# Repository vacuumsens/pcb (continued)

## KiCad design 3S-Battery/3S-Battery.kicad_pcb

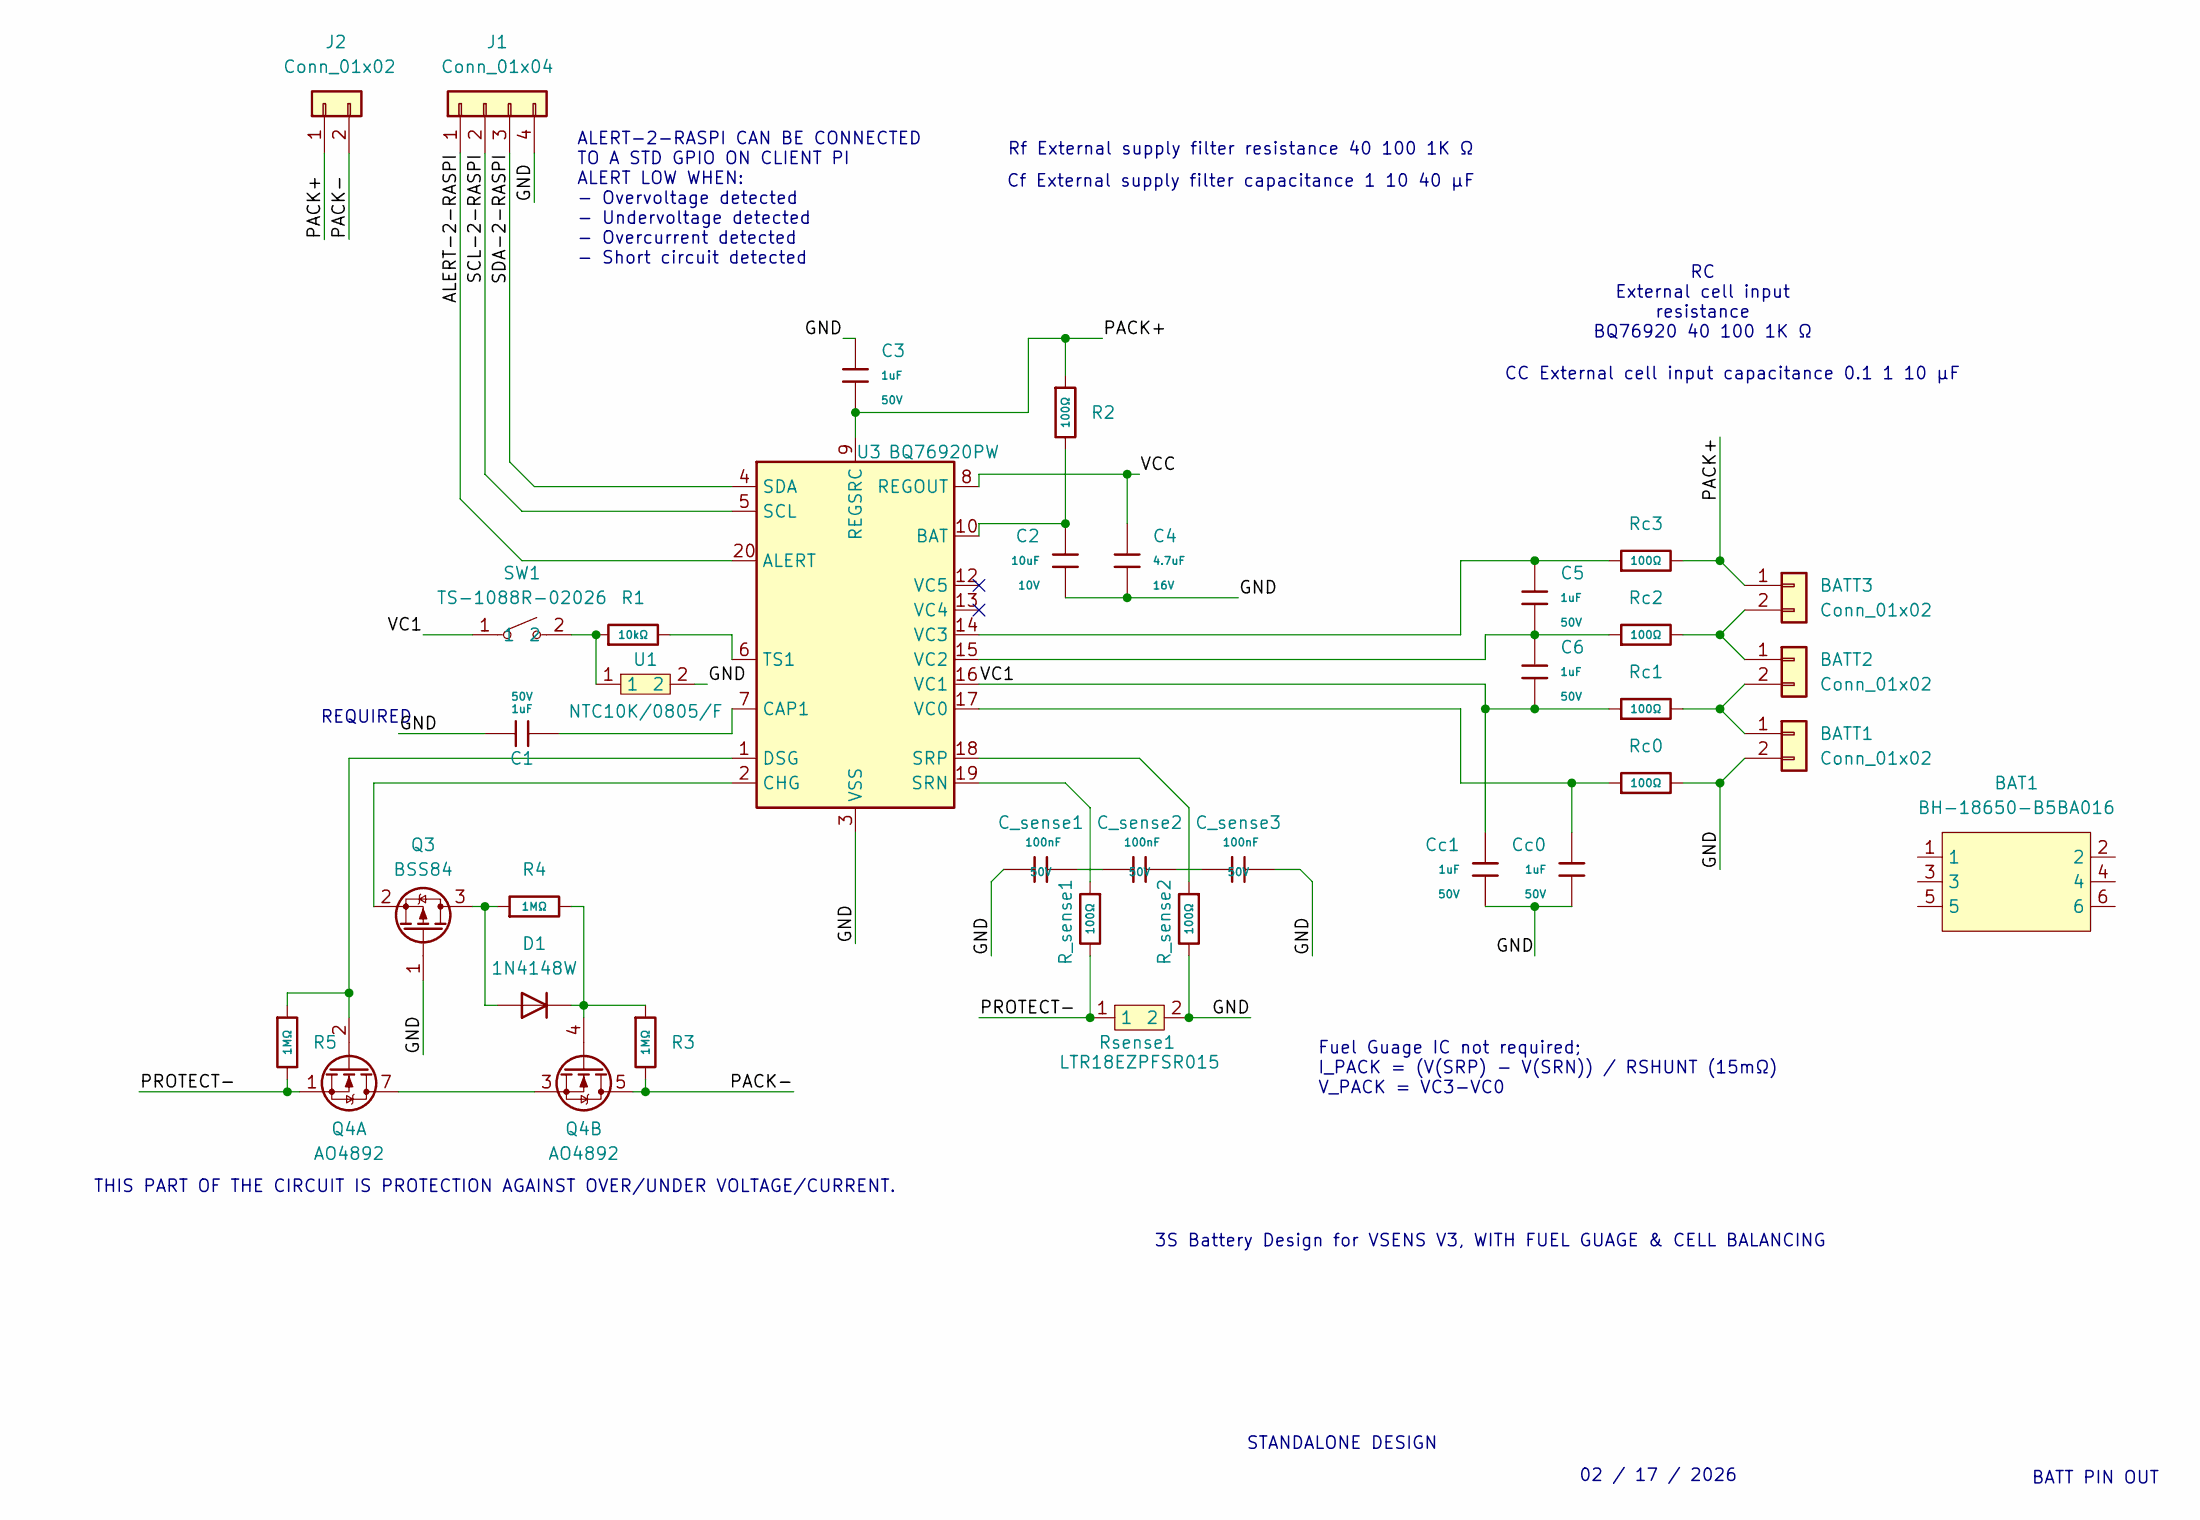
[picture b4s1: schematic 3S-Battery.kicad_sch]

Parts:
BAT1: BH-18650-B5BA016; BAT-SMD_BH-18650-B5BA016; LCSC Part C19184086
BATT1, BATT2, BATT3: Conn_01x02; PinHeader_1x02_P2.54mm_Vertical
C1: 1uF; C_1206; Voltage Rated 50V; Tolerance ±10%; Part CL31B105KBHNNNE; LCSC C1848
C2: 10uF; C_0603; Voltage Rated 10V; Tolerance ±10%; Part CL10A106KP8NNNC; LCSC C19702
C3, C5, C6: 1uF; C_0603; Voltage Rated 50V; Tolerance ±10%; Part CL10A105KB8NNNC; LCSC C15849
C4: 4.7uF; C_0603; Voltage Rated 16V; Tolerance ±10%; Part CL10A475KO8NNNC; LCSC C19666
C_sense1, C_sense2, C_sense3: 100nF; C_0603; Voltage Rated 50V; Tolerance ±10%; Part CC0603KRX7R9BB104; LCSC C14663
Cc0, Cc1: 1uF; C_0603; Voltage Rated 50V; Tolerance ±10%; Part CL10A105KB8NNNC; LCSC C15849
D1: 1N4148W; D_SOD-123
J1: Conn_01x04; PinHeader_1x04_P2.54mm_Vertical; LCSC Part C5116483
J2: Conn_01x02; PinHeader_1x02_P2.54mm_Vertical; LCSC Part C5360898
Q3: BSS84; SOT-23; LCSC Part C82079
Q4: AO4892; SOIC-8_3.9x4.9mm_P1.27mm; LCSC Part C357830
R1: 10kΩ; R_0603; Overload Voltage (Max) 75V; Tolerance ±1%; Part 0603WAF1002T5E; LCSC C25804
R2: 100Ω; R_0603; Overload Voltage (Max) 75V; Tolerance ±1%; Part 0603WAF1000T5E; LCSC C22775
R3, R4, R5: 1MΩ; R_0603; Overload Voltage (Max) 75V; Tolerance ±1%; Part 0603WAF1004T5E; LCSC C22935
R_sense1, R_sense2: 100Ω; R_0603; Overload Voltage (Max) 75V; Tolerance ±1%; Part 0603WAF1000T5E; LCSC C22775
Rc0, Rc1, Rc2, Rc3: 100Ω; R_0603; Overload Voltage (Max) 75V; Tolerance ±1%; Part 0603WAF1000T5E; LCSC C22775
Rsense1: LTR18EZPFSR015; R0612; LCSC Part C510175
SW1: TS-1088R-02026; SW-SMD_L3.9-W3.0-P4.45; LCSC Part C455280
U1: NTC10K/0805/F; R0805; LCSC Part C9900005726
U3: BQ76920PW; TSSOP-20_4.4x6.5mm_P0.65mm

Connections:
/ALERT-2-RASPI: J1.1, U3.20 (ALERT)
/GND: BATT1.2, C1.1, C2.1, C3.1, C4.2, C_sense1.1, C_sense3.2, Cc0.2, Cc1.2, J1.4, Q3.1 (G), R_sense2.2, Rc0.2, Rsense1.2, U1.2, U3.3 (VSS)
/PACK+: BATT3.1, C3.2, J2.1, R2.1, Rc3.2, U3.9 (REGSRC)
/PACK-: J2.2, Q4.5 (D2), Q4.6 (D2), R3.2
/PROTECT-: Q4.1 (S1), R5.2, R_sense1.2, Rsense1.1
/SCL-2-RASPI: J1.2, U3.5 (SCL)
/SDA-2-RASPI: J1.3, U3.4 (SDA)
/VC1: C6.2, Cc1.1, Rc1.1, SW1.1, U3.16 (VC1)
/VCC: C4.1, U3.8 (REGOUT)
unnamed: BATT1.1, BATT2.2, Rc1.2
unnamed: BATT2.1, BATT3.2, Rc2.2
unnamed: C_sense1.2, C_sense2.1
unnamed: C_sense2.2, C_sense3.1
unnamed: D1.2 (A), Q3.3 (D), R4.1
unnamed: D1.1 (K), Q4.4 (G2), R3.1, R4.2
unnamed: Q3.2 (S), U3.2 (CHG)
unnamed: Q4.2 (G1), R5.1, U3.1 (DSG)
unnamed: Q4.3 (S2), Q4.7 (D1), Q4.8 (D1)
unnamed: R1.1, SW1.2, U1.1
unnamed: C2.2, R2.2, U3.10 (BAT)
unnamed: C1.2, U3.7 (CAP1)
unnamed: R_sense1.1, U3.19 (SRN)
unnamed: R_sense2.1, U3.18 (SRP)
unnamed: R1.2, U3.6 (TS1)
unnamed: Cc0.1, Rc0.1, U3.17 (VC0)
unnamed: C5.2, C6.1, Rc2.1, U3.15 (VC2)
unnamed: C5.1, Rc3.1, U3.14 (VC3)

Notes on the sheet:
REQUIRED
02 / 17 / 2026
Fuel Guage IC not required; I_PACK = (V(SRP) - V(SRN)) / RSHUNT (15mΩ) V_PACK = VC3-VC0
STANDALONE DESIGN
RC External cell input resistance BQ76920 40 100 1K Ω
Rf External supply filter resistance 40 100 1K Ω
BATT PIN OUT
Cf External supply filter capacitance 1 10 40 µF
THIS PART OF THE CIRCUIT IS PROTECTION AGAINST OVER/UNDER VOLTAGE/CURRENT.
CC External cell input capacitance 0.1 1 10 µF
ALERT-2-RASPI CAN BE CONNECTED TO A STD GPIO ON CLIENT PI ALERT LOW WHEN: - Overvoltage detected - Undervoltage detected - Overcurrent detected - Short circuit detected
3S Battery Design for VSENS V3, WITH FUEL GUAGE & CELL BALANCING

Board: 2 copper layers, 35 parts (0 on the bottom side), 27 nets, no tracks yet.

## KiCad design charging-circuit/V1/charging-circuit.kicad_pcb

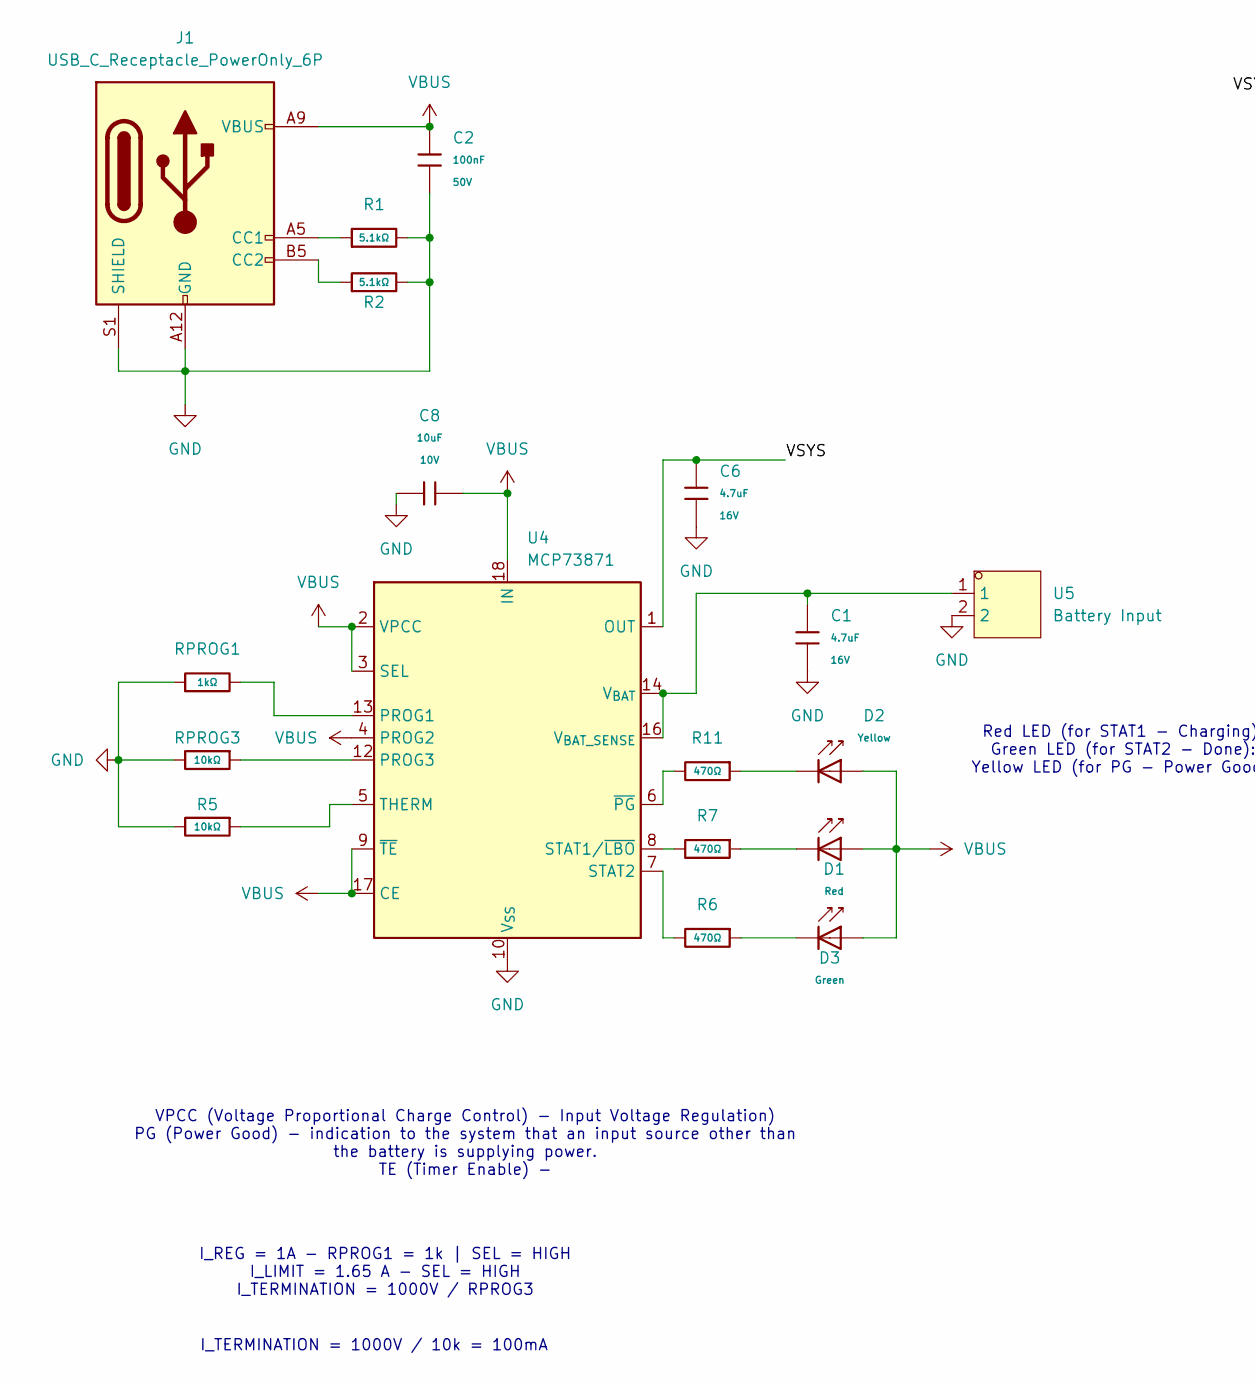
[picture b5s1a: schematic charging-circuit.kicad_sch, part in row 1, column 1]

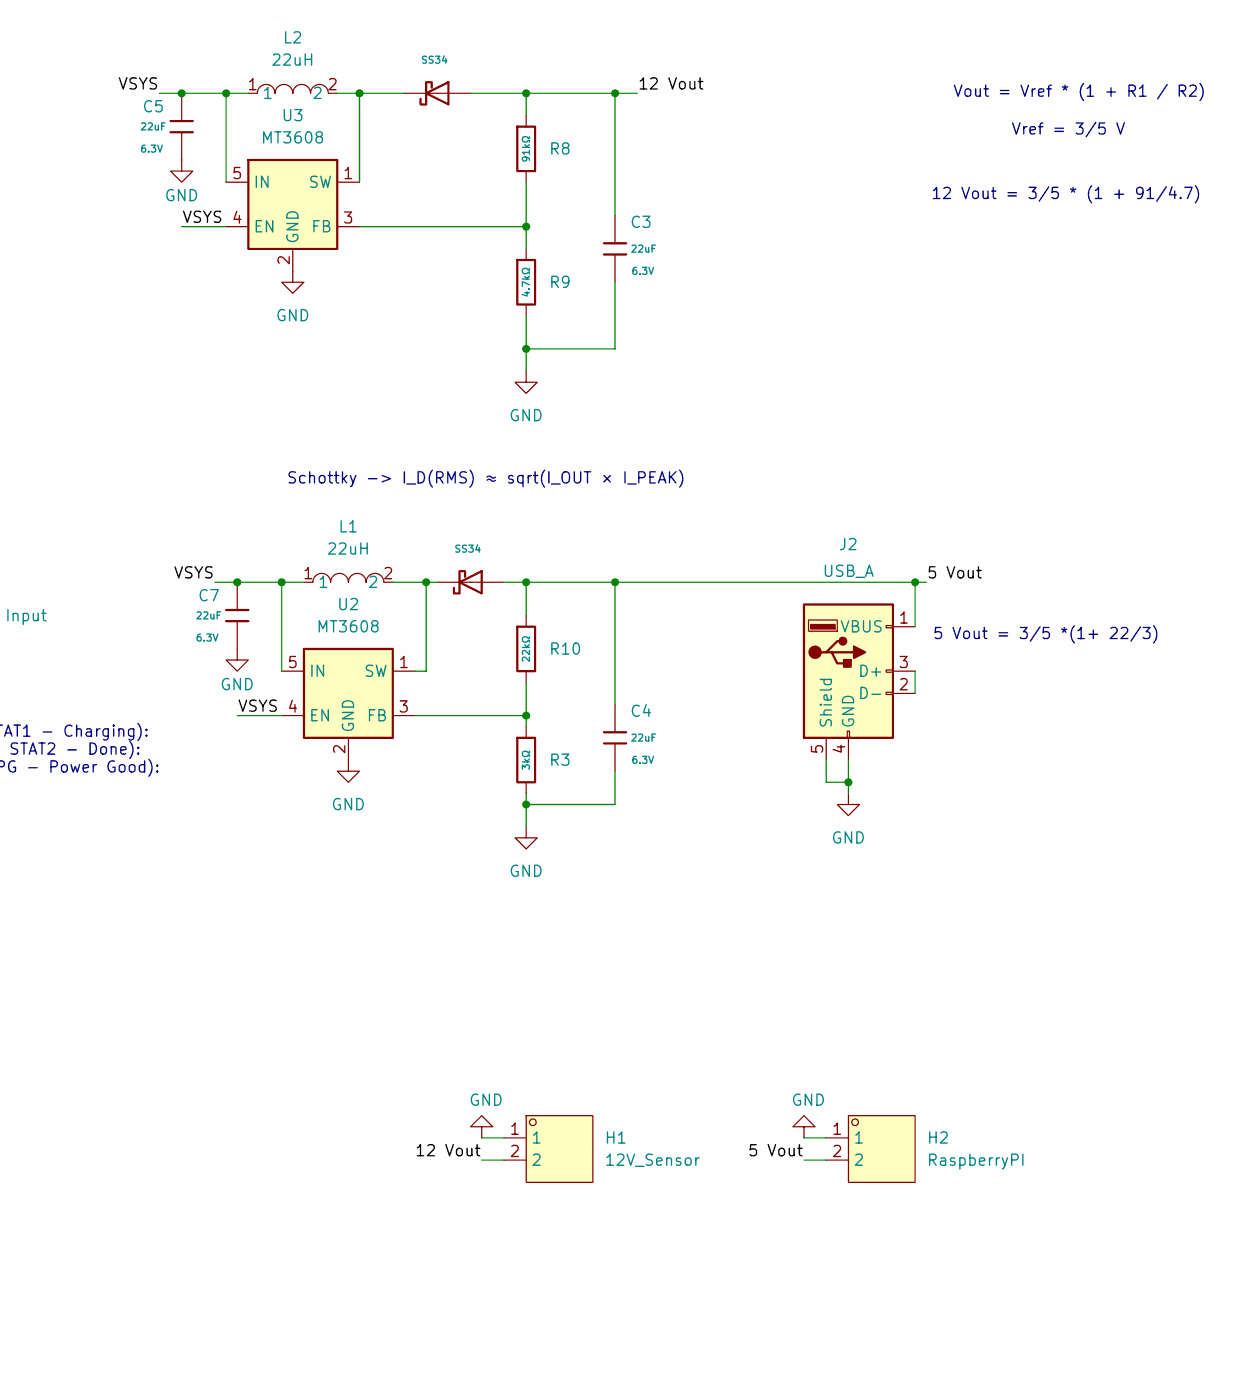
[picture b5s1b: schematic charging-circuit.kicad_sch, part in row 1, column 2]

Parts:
C1, C6: 4.7uF; C_0603; Voltage Rated 16V; Tolerance ±10%; Part CL10A475KO8NNNC; LCSC C19666
C2: 100nF; C_0603; Voltage Rated 50V; Tolerance ±10%; Part CC0603KRX7R9BB104; LCSC C14663
C3, C4, C5, C7: 22uF; C_0603; Voltage Rated 6.3V; Tolerance ±20%; Part CL10A226MQ8NRNC; LCSC C59461
C8: 10uF; C_0603; Voltage Rated 10V; Tolerance ±10%; Part CL10A106KP8NNNC; LCSC C19702
D1: Red; D_0805; Forward Voltage (VF) 1.6V~2.6V; Part NCD0805R1; LCSC C84256
D2: Yellow; D_0805; Part KT-0805Y; LCSC C2296
D3: Green; D_0805; Part KT-0805G; LCSC C2297
D4, D5: SS34; D_SMA; Forward Voltage (Vf@If) 550mV@3A; Reverse Voltage (Vr) 40V; Part SS34; LCSC C8678
H1: 12V_Sensor; HDR-TH_2P-P2.54-V-M-1; LCSC Part C124375
H2: RaspberryPI; HDR-TH_2P-P2.54-V-M-1; LCSC Part C124375
J1: USB_C_Receptacle_PowerOnly_6P; TYPE-C-SMD_TYPE-C-6P; LCSC Part C283540
J2: USB_A; USB-A-TH_AF-WJDG
L1, L2: 22uH; IND-SMD_L7.5-W7.5; LCSC Part C19268629
R1, R2: 5.1kΩ; R_0603; Overload Voltage (Max) 75V; Tolerance ±1%; Part 0603WAF5101T5E; LCSC C23186
R3: 3kΩ; R_0603; Overload Voltage (Max) 75V; Tolerance ±1%; Part 0603WAF3001T5E; LCSC C4211
R5: 10kΩ; R_0603; Overload Voltage (Max) 75V; Tolerance ±1%; Part 0603WAF1002T5E; LCSC C25804
R6, R7, R11: 470Ω; R_0603; Overload Voltage (Max) 75V; Tolerance ±1%; Part 0603WAF4700T5E; LCSC C23179
R8: 91kΩ; R_0603; Overload Voltage (Max) 75V; Tolerance ±1%; Part 0603WAF9102T5E; LCSC C23265
R9: 4.7kΩ; R_0603; Overload Voltage (Max) 75V; Tolerance ±1%; Part 0603WAF4701T5E; LCSC C23162
R10: 22kΩ; R_0603; Overload Voltage (Max) 75V; Tolerance ±1%; Part 0603WAF2202T5E; LCSC C31850
RPROG1: 1kΩ; R_0603; Overload Voltage (Max) 75V; Tolerance ±1%; Part 0603WAF1001T5E; LCSC C21190
RPROG3: 10kΩ; R_0603; Overload Voltage (Max) 75V; Tolerance ±1%; Part 0603WAF1002T5E; LCSC C25804
U2, U3: MT3608; SOT-23-6_L2.9-W1.6-P0.95-LS2.8-BL
U4: MCP73871; QFN-20_L4.0-W4.0-P0.5-BL-EP; LCSC Part C511310
U5: Battery Input; CONN-TH_S2B-PH-K-S-GW; LCSC Part C157932

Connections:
/5 Vout: C4.2, D5.2, H2.2, J2.1 (VBUS), R10.1
/12 Vout: C3.2, D4.2, H1.2, R8.1
/VSYS: C5.1, C6.2, C7.1, L1.1, L2.1, U2.4 (EN), U2.5 (IN), U3.4 (EN), U3.5 (IN), U4.1 (OUT), U4.20 (OUT)
GND: C1.1, C2.2, C3.1, C4.1, C5.2, C6.1, C7.2, C8.1, H1.1, H2.1, J1.A12 (GND), J1.B12 (GND), J1.S1 (SHIELD), J2.4 (GND), J2.5 (Shield), R1.2, R2.2, R3.2, R5.2, R9.2, RPROG1.1, RPROG3.2, U2.2 (GND), U3.2 (GND), U4.10 (V_{SS}), U4.11 (V_{SS}), U4.21 (V_{SS}), U5.2
unnamed: D1.1, R7.1
unnamed: D2.1, R11.1
unnamed: D3.1, R6.1
unnamed: J1.A5 (CC1), R1.1
unnamed: J1.B5 (CC2), R2.1
unnamed: J2.2 (D-), J2.3 (D+)
unnamed: R3.1, R10.2, U2.3 (FB)
unnamed: D5.1, L1.2, U2.1 (SW)
unnamed: R8.2, R9.1, U3.3 (FB)
unnamed: D4.1, L2.2, U3.1 (SW)
unnamed: RPROG1.2, U4.13 (PROG1)
unnamed: RPROG3.1, U4.12 (PROG3)
unnamed: R7.2, U4.8 (STAT1/~LBO)
unnamed: R6.2, U4.7 (STAT2)
unnamed: R5.1, U4.5 (THERM)
unnamed: C1.2, U4.14 (V_{BAT}), U4.15 (V_{BAT}), U4.16 (V_{BAT_SENSE}), U5.1
unnamed: R11.2, U4.6 (~PG)
VBUS: C2.1, C8.2, D1.2, D2.2, D3.2, J1.A9 (VBUS), J1.B9 (VBUS), U4.2 (VPCC), U4.3 (SEL), U4.4 (PROG2), U4.9 (~TE), U4.17 (CE), U4.18 (IN), U4.19 (IN)

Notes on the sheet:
I_REG = 1A - RPROG1 = 1k | SEL = HIGH I_LIMIT = 1.65 A - SEL = HIGH I_TERMINATION = 1000V / RPROG3
12 Vout = 3/5 * (1 + 91/4.7)
5 Vout = 3/5 *(1+ 22/3)
VPCC (Voltage Proportional Charge Control) - Input Voltage Regulation) PG (Power Good) - indication to the system that an input source other than the battery is supplying power. TE (Timer Enable) -
Schottky -> I_D(RMS) ≈ sqrt(I_OUT × I_PEAK)
I_TERMINATION = 1000V / 10k = 100mA
Vout = Vref * (1 + R1 / R2)
Red LED (for STAT1 - Charging): Green LED (for STAT2 - Done): Yellow LED (for PG - Power Good):
Vref = 3/5 V

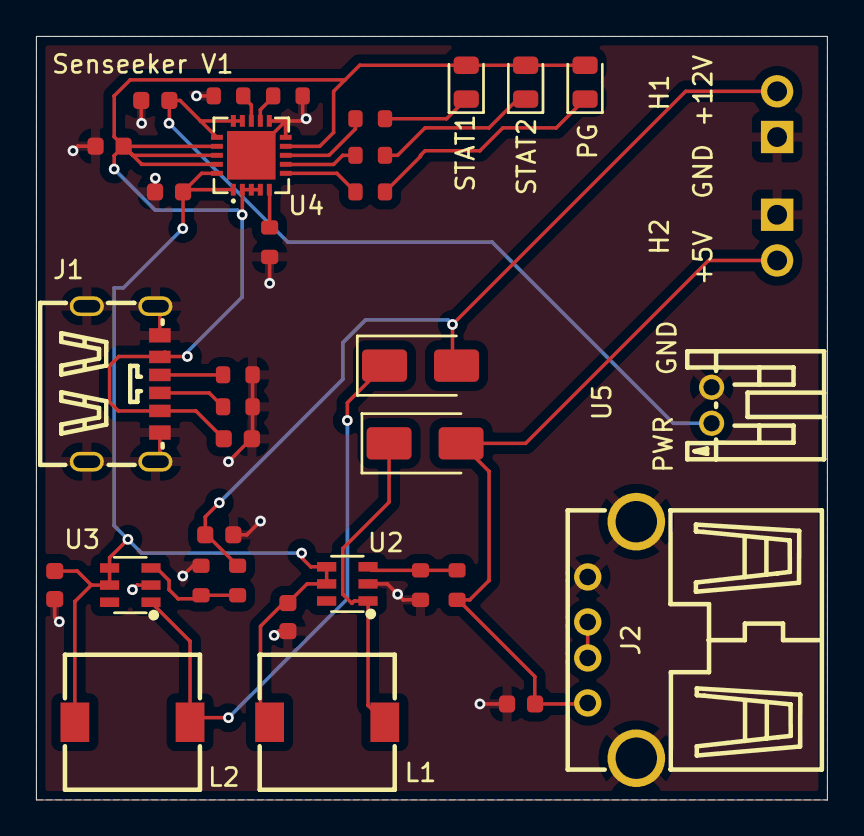
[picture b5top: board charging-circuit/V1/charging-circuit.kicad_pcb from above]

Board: 2 copper layers, 43.9 x 42.4 mm, 35 parts (0 on the bottom side), 22 nets.

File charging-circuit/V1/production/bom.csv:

Designator,Footprint,Quantity,Value,LCSC Part #
"C1, C6",C_0603,2,4.7uF,C19666
C2,C_0603,1,100nF,C14663
"C3, C4, C5, C7",C_0603,4,22uF,C59461
C8,C_0603,1,10uF,C19702
D1,D_0805,1,Red,C84256
D2,D_0805,1,Yellow,C2296
D3,D_0805,1,Green,C2297
"D4, D5",D_SMA,2,SS34,C8678
H1,HDR-TH_2P-P2.54-V-M-1,1,12V_Sensor,C124375
H2,HDR-TH_2P-P2.54-V-M-1,1,RaspberryPI,C124375
J1,TYPE-C-SMD_TYPE-C-6P,1,USB_C_Receptacle_PowerOnly_6P,C283540
J2,USB-A-TH_AF-WJDG,1,USB_A,
"L1, L2",IND-SMD_L7.5-W7.5,2,22uH,C19268629
"R1, R2",R_0603,2,5.1kΩ,C23186
R10,R_0603,1,22kΩ,C31850
"R11, R6, R7",R_0603,3,470Ω,C23179
R3,R_0603,1,3kΩ,C4211
"R5, RPROG3",R_0603,2,10kΩ,C25804
R8,R_0603,1,91kΩ,C23265
R9,R_0603,1,4.7kΩ,C23162
RPROG1,R_0603,1,1kΩ,C21190
"U2, U3",SOT-23-6_L2.9-W1.6-P0.95-LS2.8-BL,2,MT3608,
U4,QFN-20_L4.0-W4.0-P0.5-BL-EP,1,MCP73871,C511310
U5,CONN-TH_S2B-PH-K-S-GW,1,Battery Input,C157932

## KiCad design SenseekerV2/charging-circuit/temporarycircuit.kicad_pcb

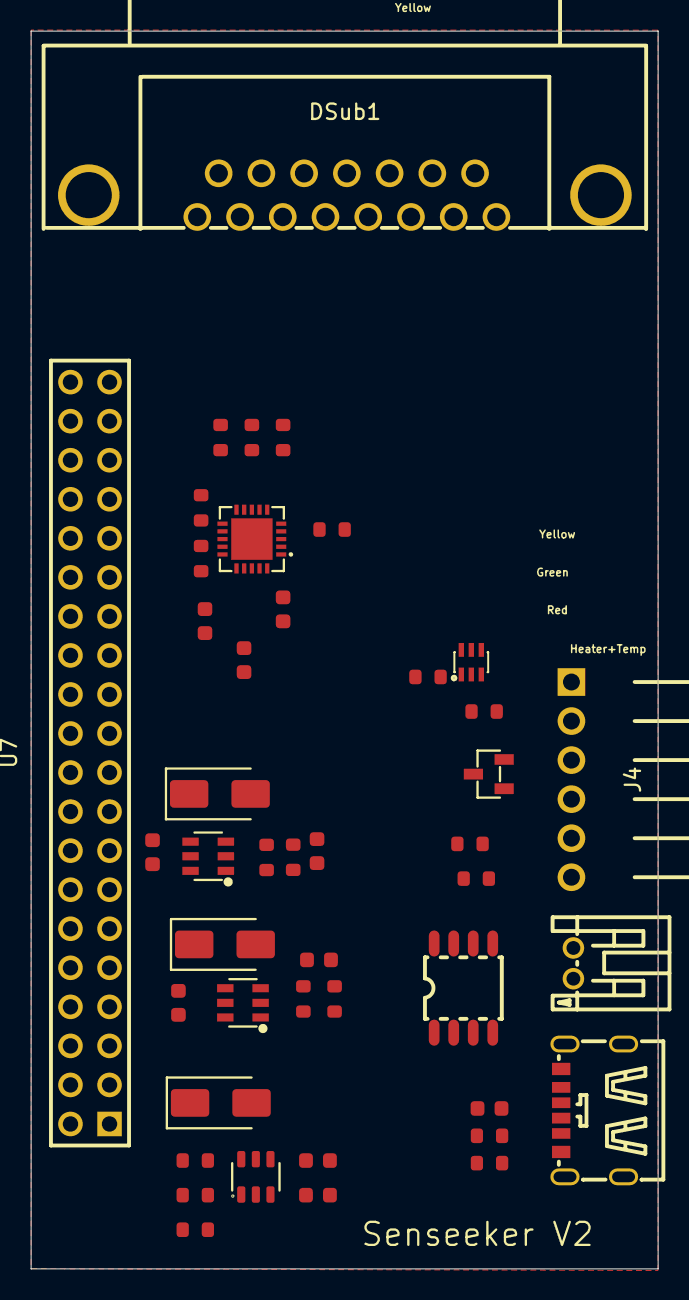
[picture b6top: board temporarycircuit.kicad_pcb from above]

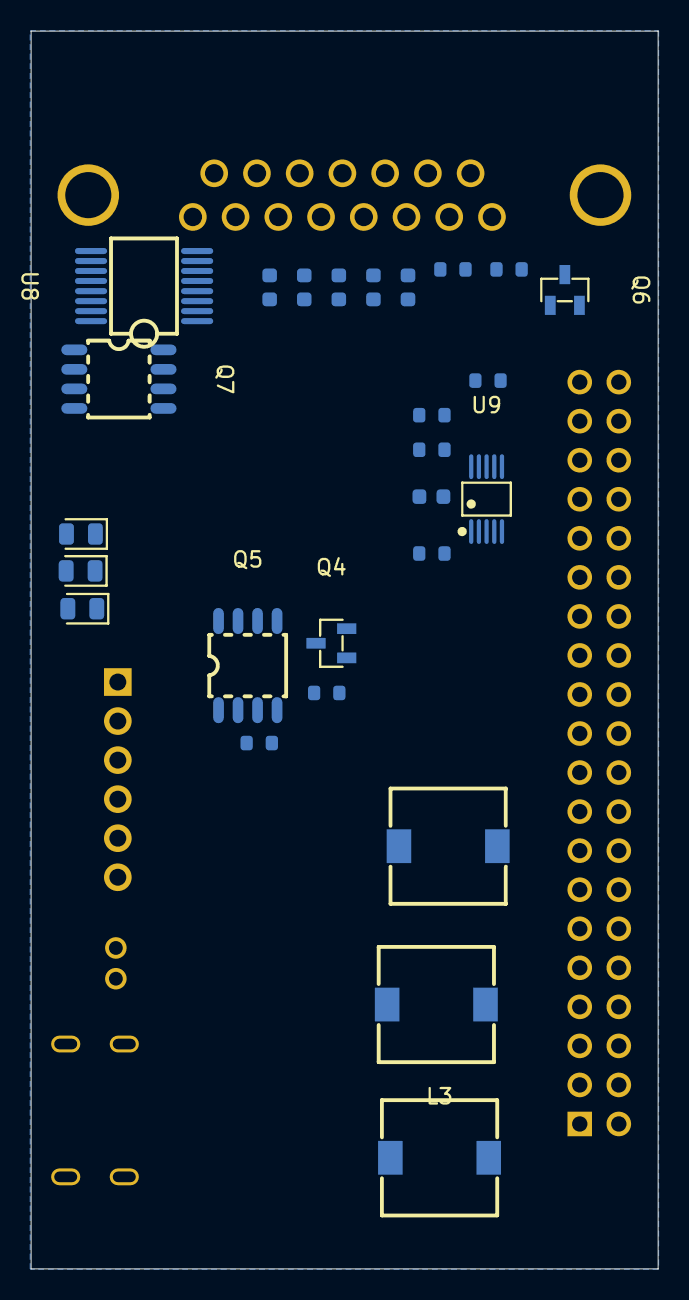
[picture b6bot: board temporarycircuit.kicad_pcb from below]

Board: 2 copper layers, 40.8 x 80.5 mm, 70 parts (26 on the bottom side), 53 nets, no tracks yet.

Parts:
C1, C6: 4.7uF; C_0603
C2, C12, C17, C18, C19, C20, C21: 100nF; C_0603
C3, C4, C5, C7, C10, C11: 22uF; C_0603
C8: 10uF; C_0603
D1: Red; D_0805
D2: Yellow; D_0805
D3: Green; D_0805
D4, D5, D6: SS34; D_SMA
DSub1: DS1037-15FNAKT74-0CC; DSUB-TH_DS1037-15FNAKT74-0CC
J1: USB_C_Receptacle_PowerOnly_6P; TYPE-C-SMD_TYPE-C-6P
J4: Heater+TempPins; HDR-TH_6P-P2.54-H-M-W10.0
L1, L2, L3: 22uH; IND-SMD_L7.5-W7.5
Q1, Q4, Q6: 2N7002; SOT-23-3_L2.9-W1.3-P1.90-LS2.4-BR
Q2, Q5, Q7: CJQ4435; SOP-8_L5.0-W4.0-P1.27-LS6.2-BL
Q3: currentmirror; SOT-363-6_L2.2-W1.3-P0.65-LS2.1-BL
R1, R2, R12, R13, R21: 5.1kΩ; R_0603
R3: 3kΩ; R_0603
R4: 20kΩ; R_0603
R5, R14, R15, R16: 10kΩ; R_0603
R6, R7, R11: 470Ω; R_0603
R8: 91kΩ; R_0603
R9: 4.7kΩ; R_0603
R10: 22kΩ; R_0603
R18: 6.8kΩ; R_0603
R19: 2kΩ; R_0603
R20: 2.2kΩ; R_0603
R22: 100Ω; R_0603
R23: 240kΩ; R_0603
RPROG1, RPROG4, RPROG5, RPROG6: 1kΩ; R_0603
RPROG3: 10kΩ; R_0603
U2, U3, U6: MT3608; SOT-23-6_L2.9-W1.6-P0.95-LS2.8-BL
U4: MCP73871; QFN-20_L4.0-W4.0-P0.5-BL-EP
U5: Battery Input; CONN-TH_S2B-PH-K-S-GW
U7: 2.54-2*20; HDR-TH_40P-P2.54-V-F-R2-C20-S2.54
U8: MAX3232CDBR; SSOP-16_L6.2-W5.3-P0.65-LS7.8-BL
U9: ADS1115IDGSR; MSOP-10_L3.0-W3.0-P0.50-LS5.0-BL

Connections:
/3.3V: C11.2, C21.1, D6.1, Q5.1 (S), Q5.2 (S), Q5.3 (S), R16.2, R18.1, U8.16 (VCC)
/5 Vout: C4.2, D5.1, R10.1, U7.2, U7.4
/12V: C3.2, D4.1, Q2.1 (S), Q2.2 (S), Q2.3 (S), Q7.1 (S), Q7.2 (S), Q7.3 (S), R8.1, R14.2, R15.2
/A0: J4.5, U9.4 (AIN0)
/A1: J4.6, U9.5 (AIN1)
/Address: R22.2, U9.1 (ADDR)
/GPIO3/SCL1: R12.2, R21.2, U7.5, U9.9 (SDA), U9.10 (SCL)
/GPIO14/TXD0: U7.8, U8.11 (DIN1)
/GPIO15/RXD0: U7.10, U8.12 (ROUT1)
/GPIO18/PCM.CLK: Q1.1 (G), U7.12
/GPIO23: Q6.1 (G), U7.16
/GPIO24: Q4.1 (G), U7.18
/Temp3.3V: C12.1, J4.4, Q5.5 (D), Q5.6 (D), Q5.7 (D), Q5.8 (D), R4.1, R12.1, R13.1, R21.1, RPROG4.1, U9.8 (VDD)
/UART_RX_13V: DSub1.1, U8.13 (RIN1)
/UART_TX_13V: DSub1.2, U8.14 (DOUT1)
/VSYS: C5.1, C6.2, C7.1, C10.1, L1.1, L2.1, L3.1, U2.4 (EN), U2.5 (IN), U3.4 (EN), U3.5 (IN), U4.1 (OUT), U4.20 (OUT), U6.4 (EN), U6.5 (IN)
/base: Q3.2 (B), Q3.5 (B), Q3.6 (C), R23.2
/raspi3.3V: U7.1, U7.17
GND: C1.1, C2.2, C3.1, C4.1, C5.2, C6.1, C7.2, C8.1, C10.2, C11.1, C12.2, C17.2, C18.2, C21.2, DSub1.4, J1.A12 (GND), J1.B12 (GND), J1.S1 (SHIELD), J4.1, Q1.2 (S), Q3.1 (E), Q3.4 (E), Q4.2 (S), Q6.2 (S), R1.2, R2.2, R3.2, R5.2, R9.2, R19.2, R22.1, RPROG1.1, RPROG3.2, RPROG4.2, RPROG5.2, RPROG6.2, U2.2 (GND), U3.2 (GND), U4.10 (V_{SS}), U4.11 (V_{SS}), U4.21 (V_{SS}), U5.2, U6.2 (GND), U7.6, U7.9, U7.14, U7.20, U7.25, U7.30, U7.34, U7.39, U8.15 (GND), U9.3 (GND)
unnamed: D1.1, R7.1
unnamed: D2.1, R11.1
unnamed: D3.1, R6.1
unnamed: DSub1.3, Q7.5 (D), Q7.6 (D), Q7.7 (D), Q7.8 (D), RPROG6.1
unnamed: J1.A5 (CC1), R1.1
unnamed: J1.B5 (CC2), R2.1
unnamed: J4.2, Q2.5 (D), Q2.6 (D), Q2.7 (D), Q2.8 (D), RPROG5.1
unnamed: J4.3, Q3.3 (C)
unnamed: Q1.3 (D), Q2.4 (G), R14.1
unnamed: Q4.3 (D), Q5.4 (G), R16.1
unnamed: Q6.3 (D), Q7.4 (G), R15.1
unnamed: R18.2, R20.1
unnamed: R4.2, R23.1
unnamed: R3.1, R10.2, U2.3 (FB)
unnamed: D5.2, L1.2, U2.1 (SW)
unnamed: R8.2, R9.1, U3.3 (FB)
unnamed: D4.2, L2.2, U3.1 (SW)
unnamed: RPROG1.2, U4.13 (PROG1)
unnamed: RPROG3.1, U4.12 (PROG3)
unnamed: R7.2, U4.8 (STAT1/~LBO)
unnamed: R6.2, U4.7 (STAT2)
unnamed: R5.1, U4.5 (THERM)
unnamed: C1.2, U4.14 (V_{BAT}), U4.15 (V_{BAT}), U4.16 (V_{BAT_SENSE}), U5.1
unnamed: R11.2, U4.6 (~PG)
unnamed: R19.1, R20.2, U6.3 (FB)
unnamed: D6.2, L3.2, U6.1 (SW)
unnamed: C20.1, U8.1 (C1+)
unnamed: C20.2, U8.3 (C1-)
unnamed: C19.1, U8.4 (C2+)
unnamed: C19.2, U8.5 (C2-)
unnamed: C18.1, U8.2 (V+)
unnamed: C17.1, U8.6 (V-)
unnamed: R13.2, U9.2 (ALERT/RDY)
VBUS: C2.1, C8.2, D1.2, D2.2, D3.2, J1.A9 (VBUS), J1.B9 (VBUS), U4.2 (VPCC), U4.3 (SEL), U4.4 (PROG2), U4.9 (~TE), U4.17 (CE), U4.18 (IN), U4.19 (IN)

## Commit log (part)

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2026-01-29 Initial commit: KiCad schematic projects
2026-01-29 Centralize easyeda2kicad library in libs/ folder
2026-01-29 Remove redundant imports folder
2026-01-29 Add README with EasyEDA import instructions
2026-01-29 Remove local EasyEDA libraries, use centralized libs/
2026-01-29 Add RS232-converter project with centralized lib references
2026-01-29 Add .gitignore for KiCad lock and temp files
2026-01-29 Remove .DS_Store files from tracking
2026-02-01 DB15 breakout board design added
2026-02-16 Initial Traces Complete
2026-02-17 Fixed DRC Thermal Errors
2026-02-17 Restructuring
2026-02-17 Final Edits to v2 before sending to Lucas
2026-02-17 bom & cpl . csv
2026-02-17 added gbr files zip
2026-02-21 Brning in pcb from front of DSUB
2026-02-22 fixed dsub
2026-02-22 cleaned
2026-02-22 Edit 3d Model Path
2026-03-03 3s battery
2026-03-06 Add new components and update existing ones in easyeda2kicad library
    - Added BAT-SMD_BH-18650-B5BA016 module for battery SMD.
    - Added HDR-TH_2P-P2.54-V-M-3 and HDR-TH_4P-P2.54-V-M-1 modules for through-hole headers.
    - Introduced R0612, R2512, and R2728 modules for resistors.
    - Updated R0805 module to reference the correct 3D model file.
    - Added RES-SMD_4P-L3.2-W1.6_CSSK0612 and RES-SMD_L6.4-W3.2-R2512 modules for SMD resistors.
    - Added SO-8_L4.9-W3.9-P1.27-LS5.9-BL module for SOIC package.
2026-03-10 kicad_sym and Pretty
2026-03-10 breakout
2026-03-10 Add BQ24170RGYR symbol and VQFN-24 footprint to EasyEDA-KiCad library
    - Introduced the BQ24170RGYR symbol with properties including reference, value, footprint, datasheet, and LCSC part number.
    - Added the VQFN-24 footprint with detailed pad and silk screen definitions for the BQ24170RGYR component.
2026-03-10 mines
2026-03-11 added devpcb
2026-03-12 3s batterry additions
2026-03-12 restructured + lunarvitals circircuit added
2026-03-12 changed PD circuit
2026-03-12 3S Archived
2026-03-12 BQ25895 circuit ref added as Onion_Feather
2026-03-12 BQ25895 3A OK
2026-03-12 renamed ?
2026-03-12 added
2026-03-12 Add WSON-6 package footprint for CSD17313Q2
    This commit introduces a new KiCad module for the WSON-6 package with dimensions L2.0-W2.0-P0.65, specifically designed for the CSD17313Q2 component. The footprint includes pads, silk screen, and fab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
2026-03-12 Add new SMD component models for KiCad
    - Created CAP-SMD_BD10.0-L10.3-W10.3-FD.kicad_mod for a surface mount capacitor.
    - Added IND-SMD_L6.7-W6.6.kicad_mod for a surface mount inductor.
    - Introduced SOD-123_L2.8-W1.8-LS3.7-RD.kicad_mod for a SOD-123 package component.
2026-03-12 ready to merge
2026-03-12 libsmerge
2026-03-12 libmerge
2026-03-12 final schematic
2026-03-13 10 of 17 modules completed
2026-03-13 Finished Traces and Aligned Modules, Just need to do Mousebites
2026-03-13 KM - Ready For Mousebites, forgot to save on prev commit
2026-03-13 completed
2026-03-15 Updated Library Paths
2026-03-15 connected VBUS1 on Charge1
2026-03-15 added reverse bias diode
2026-03-15 Add C913245 to TESTPCB libs
2026-03-15 Update charging schematic after C913245 import
2026-03-17 fixed board layout
2026-03-17 Mouse Holes replaced with Break Tabs
2026-03-17 fixed drc
2026-04-15 Modularize charging-circuit schematic
    Split the original flat KiCad schematic into hierarchical sheet files with a top-level overview.
    Preserve PCB connectivity by restoring original component references and validating that the modular netlist matches the flat backup.
    Include the modularization guide, sheet interfaces, and safety backups for the migrated design.
2026-04-15 Added LM2596 module to sheet
2026-04-17 fixed ? in LM2596
2026-04-21 added 5V buck
2026-04-22 Add TO-263-5 package footprint to easyeda2kicad library
    - Created new footprint for TO-263-5_L10.2-W8.9-P1.70-TL
    - Defined pads, silkscreen, and courtyard outlines
    - Included 3D model reference for visualization
    - Added LCSC part property for component identification
2026-04-22 Fixed issue with footprint not showing up and took off potentiometer
2026-04-22 changed to 5v
2026-04-22 added pin 6 to gnd
2026-04-22 created VSENS V3
2026-04-23 Refactor code structure for improved readability and maintainability
2026-04-29 more intilaization
2026-04-30 Fixed formatting issues, now the hierachal sheets are all labeled as net labels and when we want to expose their pins we will make them into hierchal or global pins
2026-04-30 deleted and refromatted files
2026-04-30 deleted final
2026-04-30 formatting changes for LM2596, now ready to branch of off and make our seperate PCB and then compare
2026-04-30 updating to kicad 10.0
2026-04-30 added to gitignore
2026-04-30 added C5250964 CS100UF50V
2026-04-30 added 100 uF capacitor
2026-04-30 imported C5250961 VT220UF25V
2026-04-30 added 220uF cap
2026-04-30 added 100 uF cap
2026-04-30 import C8678
2026-04-30 added parts
2026-04-30 EASY EDA API could not find C1329596 so copilot just manually added it (same footprint L_Bourns_SRR1208_12.7x12.7mm)
2026-04-30 added KT-0603R LED
2026-05-02 added to gitginore
2026-05-02 added 470µF 35V SMD electrolytic capacitor.
2026-05-02 added through hole SChgottky diode
2026-05-02 220µF 25V through-hole electrolytic capacito
2026-05-02 added 470µF 50V
2026-05-02 fixed annotations
2026-05-02 5V Done
2026-05-02 added and finished 3.3V buck
2026-05-02 added the IP2326
2026-05-02 finished 3S IP2326
2026-05-02 renamed and deleted old bad name of ip2326
2026-05-02 finished USB C
2026-05-02 deleted old 3s
2026-05-03 finished for tn
2026-05-03 sunday
2026-05-03 schem
2026-05-04 Voltage Regulators Wired
2026-05-04 Finished Everything Except For Ground and USBC Errors
2026-05-04 finished
2026-05-05 tuesday
2026-05-05 labeled
2026-05-06 Added More Global Model Paths and Toggled Do Not Propogate for Test Points
2026-05-06 Forgot to save the edits
2026-05-06 Converted Important Placement parts to Step files instead of wrl
2026-05-06 4 layer
2026-05-13 changed instances of incorrect directories for 3d models to EASYEDA2KICAD
2026-05-13 Fixed all 3D model path issues in 4 PCB files and 25 footprint files across the workspace. Replaced ${EASYeda2KICAD}, ${easyeda2kicad}, and hardcoded C:/Users/abdul/Documents/V4/libs paths — all now 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
